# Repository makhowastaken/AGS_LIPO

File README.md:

# AGS_LIPO

LiPo adapter for Game Boy Advance SP. The idea behind this design is that the board itself is intended to be slightly oversized so that you may wedge it in the battery compartment against the spring contacts. The battery cell itself should not be structural or load bearing in any way.

One single board does not meet OSHpark's minimum PCB size requirement so I've uploaded two variants of the file, the single, regular version and then the same thing but I copy\pasted the same board into the file. This works for OSHpark but probably will not work for other fabs. 

Works well with 603048 batteries: https://www.aliexpress.com/item/33001664276.html (but there may be higher quality or cheaper options (or both))

# V1.0

Needs no extra parts beyond a battery itself. Order PCBs from OSHpark or download the PCB files here for using with your preferred fab. ENIG is highly recommended for this. [https://oshpark.com/shared_projects/gaB93JkC](https://oshpark.com/shared_projects/gaB93JkC)

Or order straight from RGRS: [https://retrogamerepairshop.com/collections/makho/products/gba-sp-game-boy-advance-sp-rechargeable-850mah-lipo-battery-mod-by-makho](https://retrogamerepairshop.com/collections/makho/products/gba-sp-game-boy-advance-sp-rechargeable-850mah-lipo-battery-mod-by-makho)
* Note that the original "makho battery mod" is no longer available from RGRS as it has been replaced with the spiritual successor from funnyplaying. Consider it v3 ;)

For more info and for the install, see this youtube video: [https://youtu.be/VjnONhSVvpA](https://youtu.be/VjnONhSVvpA)

# V2.0

For more info and for the install, see this youtube video: [https://youtu.be/uIvCC7yzNTQ](https://youtu.be/uIvCC7yzNTQ)

This variant is intended for use with Retromodding's 3D printable bracket: [https://www.thingiverse.com/thing:4624968](https://www.thingiverse.com/thing:4624968)

You can order PCBs here: [https://oshpark.com/shared_projects/hciypfPv](https://oshpark.com/shared_projects/uh1rTSxD)

Purchase one pre-assembled directly from Retromodding: [https://www.retromodding.com/collections/featured-items/products/makho-game-boy-advance-sp-battery](https://www.retromodding.com/collections/featured-items/products/makho-game-boy-advance-sp-battery)
* I'd recommend the [funnyplaying battery](https://retrogamerepairshop.com/collections/makho/products/gba-sp-game-boy-advance-sp-rechargeable-850mah-lipo-battery-mod-by-makho) from RGRS over the RM one linked above. Consider it v3 ;)

Bonus, this battery mod also works perfectly in the original DS (as is) and the DS Lite (rotated) as picture below ([credit](https://www.reddit.com/r/Gameboy/comments/hnpqkj/got_extra_lipos_and_makho_pcbs_fits_well_in_the/) from u/deep_size)

Simply order the v1 version boards and 603048 battery cells and assemble accordingly. There is no "framed" version of this mod for DS consoles.

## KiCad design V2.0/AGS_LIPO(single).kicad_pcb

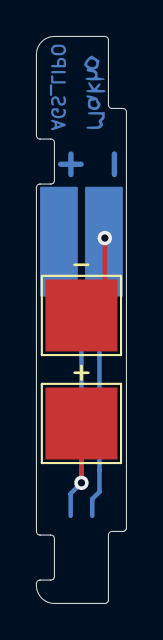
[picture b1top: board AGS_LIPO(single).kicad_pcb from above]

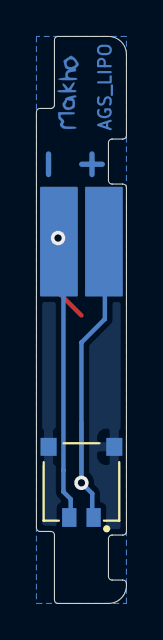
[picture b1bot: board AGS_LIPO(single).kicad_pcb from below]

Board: 2 copper layers, 5.0 x 31.5 mm, 4 parts (2 on the bottom side), 3 nets.

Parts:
+: TestPoint; TestPoint_Pad_4.0x4.0mm
-: TestPoint; TestPoint_Pad_4.0x4.0mm
J1: BM02B-ACHSS-GAN-TF(LF)(SN); JST_BM02B-ACHSS-GAN-TF(LF)(SN)
Ref**: Val**; makho_micro_fmask

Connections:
GND: J1.S1, J1.S2
unnamed: +.1, J1.1
unnamed: -.1, J1.2

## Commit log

2020-02-15 Create LICENSE
2020-05-09 Add files via upload
    added text cutout to solder mask to make orientation markings more clear
2020-05-09 Add files via upload
    updated render with new PCB design (made text more visible)
2020-05-09 Update README.md
    updated oshpark link
2020-10-18 added v2.0
